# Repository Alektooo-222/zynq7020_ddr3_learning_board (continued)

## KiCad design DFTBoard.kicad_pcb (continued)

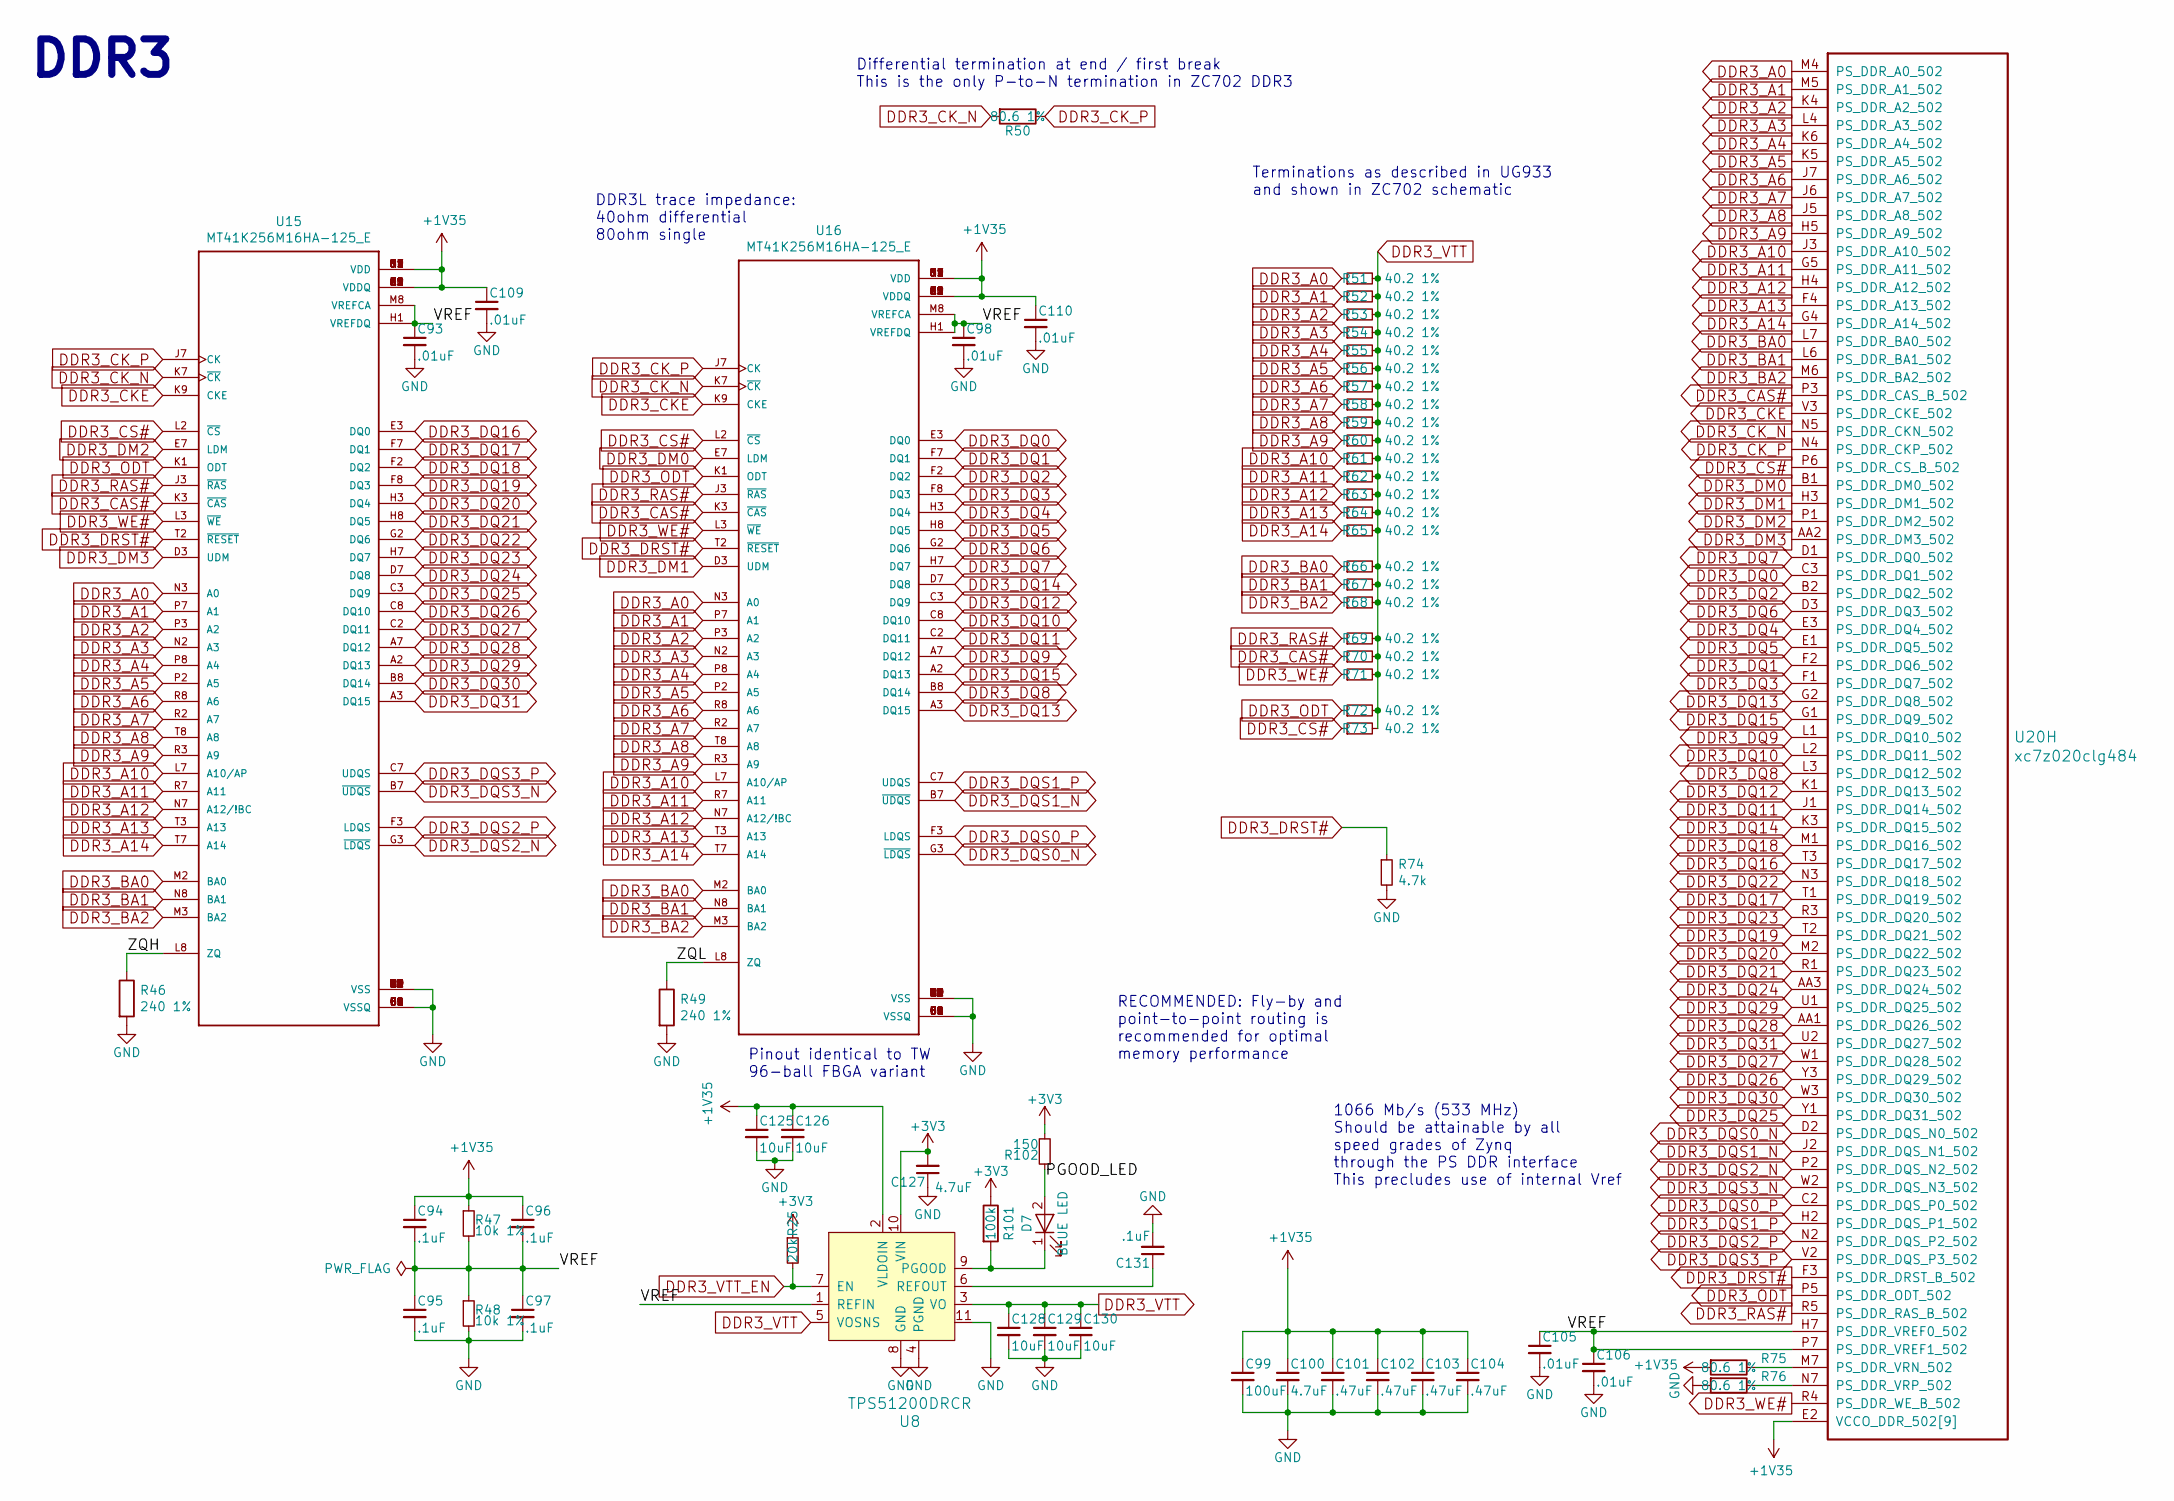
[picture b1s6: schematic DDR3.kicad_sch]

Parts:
C93, C98, C105, C106, C109, C110: .01uF; C_0402_1005Metric; MPN GRM155R71H103KA88J
C94, C95, C96, C97, C131: .1uF; C_0402_1005Metric; MPN CC0402KRX7R6BB104
C99: 100uF; C_1210_3225Metric; MPN JMK325ABJ107MM-P
C100, C127: 4.7uF; C_0402_1005Metric; MPN GRM155R60G475ME47D
C101, C102, C103, C104: .47uF; C_0402_1005Metric; MPN CC0402KRX5R5BB474
C125, C126, C128, C129, C130: 10uF; C_0603_1608Metric; MPN GRM188R61A106KE69J
D7: BLUE LED; C_0603_1608Metric; MPN VLMB1300-GS08
R25: 20k; R_0402_1005Metric; MPN RT0402BRD0720KL
R46, R49: 240 1%; R_0402_1005Metric; MPN RC0402FR-07240RL
R47, R48: 10k 1%; R_0402_1005Metric; MPN RC0402FR-0710KL
R50, R75, R76: 80.6 1%; R_0402_1005Metric; MPN RC0402FR-0780R6L
R51, R52, R53, R54, R55, R56, R57, R58, R59, R60, R61, R62, R63, R64, R65, R66, R67, R68, R69, R70, R71, R72, R73: 40.2 1%; R_0402_1005Metric; MPN RC0402FR-0740R2L
R74: 4.7k; R_0402_1005Metric; MPN RC0402JR-074K7L
R101: 100k; R_0402_1005Metric; MPN RC0402FR-07100KL
R102: 150; R_0402_1005Metric; MPN RC0402FR-07150RL
U8: TPS51200DRCR; VSON-10-1EP_3x3mm_P0.5mm_EP1.65x2.4mm_ThermalVias; MPN TPS51200DRCR; Digi-Key_PN 296-26978-1-ND
U15, U16: MT41K256M16HA-125_E; FBGA-96-DDR3-SDRAM; MPN MT41K256M16TW-107
U20: xc7z020clg484; BGA-484_19.0x19.0mm_Layout22x22_P0.80mm_dia0.40mm; MPN XC7Z020-1CLG484C

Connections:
+1V35: C94.1, C96.1, C99.1, C100.1, C101.1, C102.1, C103.1, C104.1, C109.1, C110.1, C125.1, C126.1, R47.1, R75.2, U8.2 (VLDOIN), U15.A1 (VDDQ), U15.A8 (VDDQ), U15.B2 (VDD), U15.C1 (VDDQ), U15.C9 (VDDQ), U15.D2 (VDDQ), U15.D9 (VDD), U15.E9 (VDDQ), U15.F1 (VDDQ), U15.G7 (VDD), U15.H2 (VDDQ), U15.H9 (VDDQ), U15.K2 (VDD), U15.K8 (VDD), U15.N1 (VDD), U15.N9 (VDD), U15.R1 (VDD), U15.R9 (VDD), U16.A1 (VDDQ), U16.A8 (VDDQ), U16.B2 (VDD), U16.C1 (VDDQ), U16.C9 (VDDQ), U16.D2 (VDDQ), U16.D9 (VDD), U16.E9 (VDDQ), U16.F1 (VDDQ), U16.G7 (VDD), U16.H2 (VDDQ), U16.H9 (VDDQ), U16.K2 (VDD), U16.K8 (VDD), U16.N1 (VDD), U16.N9 (VDD), U16.R1 (VDD), U16.R9 (VDD), U20.E2 (VCCO_DDR_502[9]), U20.F5 (VCCO_DDR_502[9]), U20.H1 (VCCO_DDR_502[9]), U20.J4 (VCCO_DDR_502[9]), U20.K7 (VCCO_DDR_502[9]), U20.M3 (VCCO_DDR_502[9]), U20.N6 (VCCO_DDR_502[9]), U20.R2 (VCCO_DDR_502[9]), U20.V1 (VCCO_DDR_502[9]); also elsewhere on the board
+3V3: C127.2, R25.1, R101.1, R102.2, U8.10 (VIN); also elsewhere on the board
/DDR3/PGOOD_LED: D7.2 (A), R102.1
/DDR3/VREF: C93.1, C94.2, C95.1, C96.2, C97.1, C98.1, C105.1, C106.1, R47.2, R48.1, U8.1 (REFIN), U15.H1 (VREFDQ), U15.M8 (VREFCA), U16.H1 (VREFDQ), U16.M8 (VREFCA), U20.H7 (PS_DDR_VREF0_502), U20.P7 (PS_DDR_VREF1_502)
/DDR3/ZQH: R46.1, U15.L8 (ZQ)
/DDR3/ZQL: R49.1, U16.L8 (ZQ)
DDR3_A0: R51.1, U15.N3 (A0), U16.N3 (A0), U20.M4 (PS_DDR_A0_502)
DDR3_A1: R52.1, U15.P7 (A1), U16.P7 (A1), U20.M5 (PS_DDR_A1_502)
DDR3_A2: R53.1, U15.P3 (A2), U16.P3 (A2), U20.K4 (PS_DDR_A2_502)
DDR3_A3: R54.1, U15.N2 (A3), U16.N2 (A3), U20.L4 (PS_DDR_A3_502)
DDR3_A4: R55.1, U15.P8 (A4), U16.P8 (A4), U20.K6 (PS_DDR_A4_502)
DDR3_A5: R56.1, U15.P2 (A5), U16.P2 (A5), U20.K5 (PS_DDR_A5_502)
DDR3_A6: R57.1, U15.R8 (A6), U16.R8 (A6), U20.J7 (PS_DDR_A6_502)
DDR3_A7: R58.1, U15.R2 (A7), U16.R2 (A7), U20.J6 (PS_DDR_A7_502)
DDR3_A8: R59.1, U15.T8 (A8), U16.T8 (A8), U20.J5 (PS_DDR_A8_502)
DDR3_A9: R60.1, U15.R3 (A9), U16.R3 (A9), U20.H5 (PS_DDR_A9_502)
DDR3_A10: R61.1, U15.L7 (A10/AP), U16.L7 (A10/AP), U20.J3 (PS_DDR_A10_502)
DDR3_A11: R62.1, U15.R7 (A11), U16.R7 (A11), U20.G5 (PS_DDR_A11_502)
DDR3_A12: R63.1, U15.N7 (A12/!BC), U16.N7 (A12/!BC), U20.H4 (PS_DDR_A12_502)
DDR3_A13: R64.1, U15.T3 (A13), U16.T3 (A13), U20.F4 (PS_DDR_A13_502)
DDR3_A14: R65.1, U15.T7 (A14), U16.T7 (A14), U20.G4 (PS_DDR_A14_502)
DDR3_BA0: R66.1, U15.M2 (BA0), U16.M2 (BA0), U20.L7 (PS_DDR_BA0_502)
DDR3_BA1: R67.1, U15.N8 (BA1), U16.N8 (BA1), U20.L6 (PS_DDR_BA1_502)
DDR3_BA2: R68.1, U15.M3 (BA2), U16.M3 (BA2), U20.M6 (PS_DDR_BA2_502)
DDR3_CAS#: R70.1, U15.K3 (~CAS), U16.K3 (~CAS), U20.P3 (PS_DDR_CAS_B_502)
DDR3_CKE: U15.K9 (CKE), U16.K9 (CKE), U20.V3 (PS_DDR_CKE_502)
DDR3_CK_N: R50.2, U15.K7 (~CK), U16.K7 (~CK), U20.N5 (PS_DDR_CKN_502)
DDR3_CK_P: R50.1, U15.J7 (CK), U16.J7 (CK), U20.N4 (PS_DDR_CKP_502)
DDR3_CS#: R73.1, U15.L2 (~CS), U16.L2 (~CS), U20.P6 (PS_DDR_CS_B_502)
DDR3_DM0: U16.E7 (LDM), U20.B1 (PS_DDR_DM0_502)
DDR3_DM1: U16.D3 (UDM), U20.H3 (PS_DDR_DM1_502)
DDR3_DM2: U15.E7 (LDM), U20.P1 (PS_DDR_DM2_502)
DDR3_DM3: U15.D3 (UDM), U20.AA2 (PS_DDR_DM3_502)
DDR3_DQ0: U16.E3 (DQ0), U20.C3 (PS_DDR_DQ1_502)
DDR3_DQ1: U16.F7 (DQ1), U20.F2 (PS_DDR_DQ6_502)
DDR3_DQ2: U16.F2 (DQ2), U20.B2 (PS_DDR_DQ2_502)
DDR3_DQ3: U16.F8 (DQ3), U20.F1 (PS_DDR_DQ7_502)
DDR3_DQ4: U16.H3 (DQ4), U20.E3 (PS_DDR_DQ4_502)
DDR3_DQ5: U16.H8 (DQ5), U20.E1 (PS_DDR_DQ5_502)
DDR3_DQ6: U16.G2 (DQ6), U20.D3 (PS_DDR_DQ3_502)
DDR3_DQ7: U16.H7 (DQ7), U20.D1 (PS_DDR_DQ0_502)
DDR3_DQ8: U16.B8 (DQ14), U20.L3 (PS_DDR_DQ12_502)
DDR3_DQ9: U16.A7 (DQ12), U20.L1 (PS_DDR_DQ10_502)
DDR3_DQ10: U16.C8 (DQ10), U20.L2 (PS_DDR_DQ11_502)
DDR3_DQ11: U16.C2 (DQ11), U20.J1 (PS_DDR_DQ14_502)
DDR3_DQ12: U16.C3 (DQ9), U20.K1 (PS_DDR_DQ13_502)
DDR3_DQ13: U16.A3 (DQ15), U20.G2 (PS_DDR_DQ8_502)
DDR3_DQ14: U16.D7 (DQ8), U20.K3 (PS_DDR_DQ15_502)
DDR3_DQ15: U16.A2 (DQ13), U20.G1 (PS_DDR_DQ9_502)
DDR3_DQ16: U15.E3 (DQ0), U20.T3 (PS_DDR_DQ17_502)
DDR3_DQ17: U15.F7 (DQ1), U20.T1 (PS_DDR_DQ19_502)
DDR3_DQ18: U15.F2 (DQ2), U20.M1 (PS_DDR_DQ16_502)
DDR3_DQ19: U15.F8 (DQ3), U20.T2 (PS_DDR_DQ21_502)
DDR3_DQ20: U15.H3 (DQ4), U20.M2 (PS_DDR_DQ22_502)
DDR3_DQ21: U15.H8 (DQ5), U20.R1 (PS_DDR_DQ23_502)
DDR3_DQ22: U15.G2 (DQ6), U20.N3 (PS_DDR_DQ18_502)
DDR3_DQ23: U15.H7 (DQ7), U20.R3 (PS_DDR_DQ20_502)
DDR3_DQ24: U15.D7 (DQ8), U20.AA3 (PS_DDR_DQ24_502)
DDR3_DQ25: U15.C3 (DQ9), U20.Y1 (PS_DDR_DQ31_502)
DDR3_DQ26: U15.C8 (DQ10), U20.Y3 (PS_DDR_DQ29_502)
DDR3_DQ27: U15.C2 (DQ11), U20.W1 (PS_DDR_DQ28_502)
DDR3_DQ28: U15.A7 (DQ12), U20.AA1 (PS_DDR_DQ26_502)
DDR3_DQ29: U15.A2 (DQ13), U20.U1 (PS_DDR_DQ25_502)
DDR3_DQ30: U15.B8 (DQ14), U20.W3 (PS_DDR_DQ30_502)
DDR3_DQ31: U15.A3 (DQ15), U20.U2 (PS_DDR_DQ27_502)
DDR3_DQS0_N: U16.G3 (~LDQS), U20.D2 (PS_DDR_DQS_N0_502)
DDR3_DQS0_P: U16.F3 (LDQS), U20.C2 (PS_DDR_DQS_P0_502)
DDR3_DQS1_N: U16.B7 (~UDQS), U20.J2 (PS_DDR_DQS_N1_502)
DDR3_DQS1_P: U16.C7 (UDQS), U20.H2 (PS_DDR_DQS_P1_502)
DDR3_DQS2_N: U15.G3 (~LDQS), U20.P2 (PS_DDR_DQS_N2_502)
DDR3_DQS2_P: U15.F3 (LDQS), U20.N2 (PS_DDR_DQS_P2_502)
DDR3_DQS3_N: U15.B7 (~UDQS), U20.W2 (PS_DDR_DQS_N3_502)
DDR3_DQS3_P: U15.C7 (UDQS), U20.V2 (PS_DDR_DQS_P3_502)
DDR3_DRST#: R74.1, U15.T2 (~RESET), U16.T2 (~RESET), U20.F3 (PS_DDR_DRST_B_502)
DDR3_ODT: R72.1, U15.K1 (ODT), U16.K1 (ODT), U20.P5 (PS_DDR_ODT_502)
DDR3_RAS#: R69.1, U15.J3 (~RAS), U16.J3 (~RAS), U20.R5 (PS_DDR_RAS_B_502)
DDR3_VTT: C128.1, C129.1, C130.1, R51.2, R52.2, R53.2, R54.2, R55.2, R56.2, R57.2, R58.2, R59.2, R60.2, R61.2, R62.2, R63.2, R64.2, R65.2, R66.2, R67.2, R68.2, R69.2, R70.2, R71.2, R72.2, R73.2, U8.3 (VO), U8.5 (VOSNS)
DDR3_VTT_EN: R25.2, U8.7 (EN); also elsewhere on the board
DDR3_WE#: R71.1, U15.L3 (~WE), U16.L3 (~WE), U20.R4 (PS_DDR_WE_B_502)
GND: C93.2, C95.2, C97.2, C98.2, C99.2, C100.2, C101.2, C102.2, C103.2, C104.2, C105.2, C106.2, C109.2, C110.2, C125.2, C126.2, C127.1, C128.2, C129.2, C130.2, C131.2, R46.2, R48.2, R49.2, R74.2, R76.2, U8.4 (PGND), U8.8 (GND), U8.11, U15.A9 (VSS), U15.B1 (VSSQ), U15.B3 (VSS), U15.B9 (VSSQ), U15.D1 (VSSQ), U15.D8 (VSSQ), U15.E1 (VSS), U15.E2 (VSSQ), U15.E8 (VSSQ), U15.F9 (VSSQ), U15.G1 (VSSQ), U15.G8 (VSS), U15.G9 (VSSQ), U15.J2 (VSS), U15.J8 (VSS), U15.M1 (VSS), U15.M9 (VSS), U15.P1 (VSS), U15.P9 (VSS), U15.T1 (VSS), U15.T9 (VSS), U16.A9 (VSS), U16.B1 (VSSQ), U16.B3 (VSS), U16.B9 (VSSQ), U16.D1 (VSSQ), U16.D8 (VSSQ), U16.E1 (VSS), U16.E2 (VSSQ), U16.E8 (VSSQ), U16.F9 (VSSQ), U16.G1 (VSSQ), U16.G8 (VSS), U16.G9 (VSSQ), U16.J2 (VSS), U16.J8 (VSS), U16.M1 (VSS), U16.M9 (VSS), U16.P1 (VSS), U16.P9 (VSS), U16.T1 (VSS), U16.T9 (VSS); also elsewhere on the board
unnamed: D7.1 (K), R101.2, U8.9 (PGOOD)
unnamed: C131.1, U8.6 (REFOUT)
unnamed: R75.1, U20.M7 (PS_DDR_VRN_502)
unnamed: R76.1, U20.N7 (PS_DDR_VRP_502)

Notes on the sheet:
1066 Mb/s (533 MHz) Should be attainable by all speed grades of Zynq through the PS DDR interface This precludes use of internal Vref
DDR3L trace impedance: 40ohm differential 80ohm single
Terminations as described in UG933 and shown in ZC702 schematic
Pinout identical to TW 96-ball FBGA variant
RECOMMENDED: Fly-by and point-to-point routing is recommended for optimal memory performance
DDR3
Differential termination at end / first break This is the only P-to-N termination in ZC702 DDR3

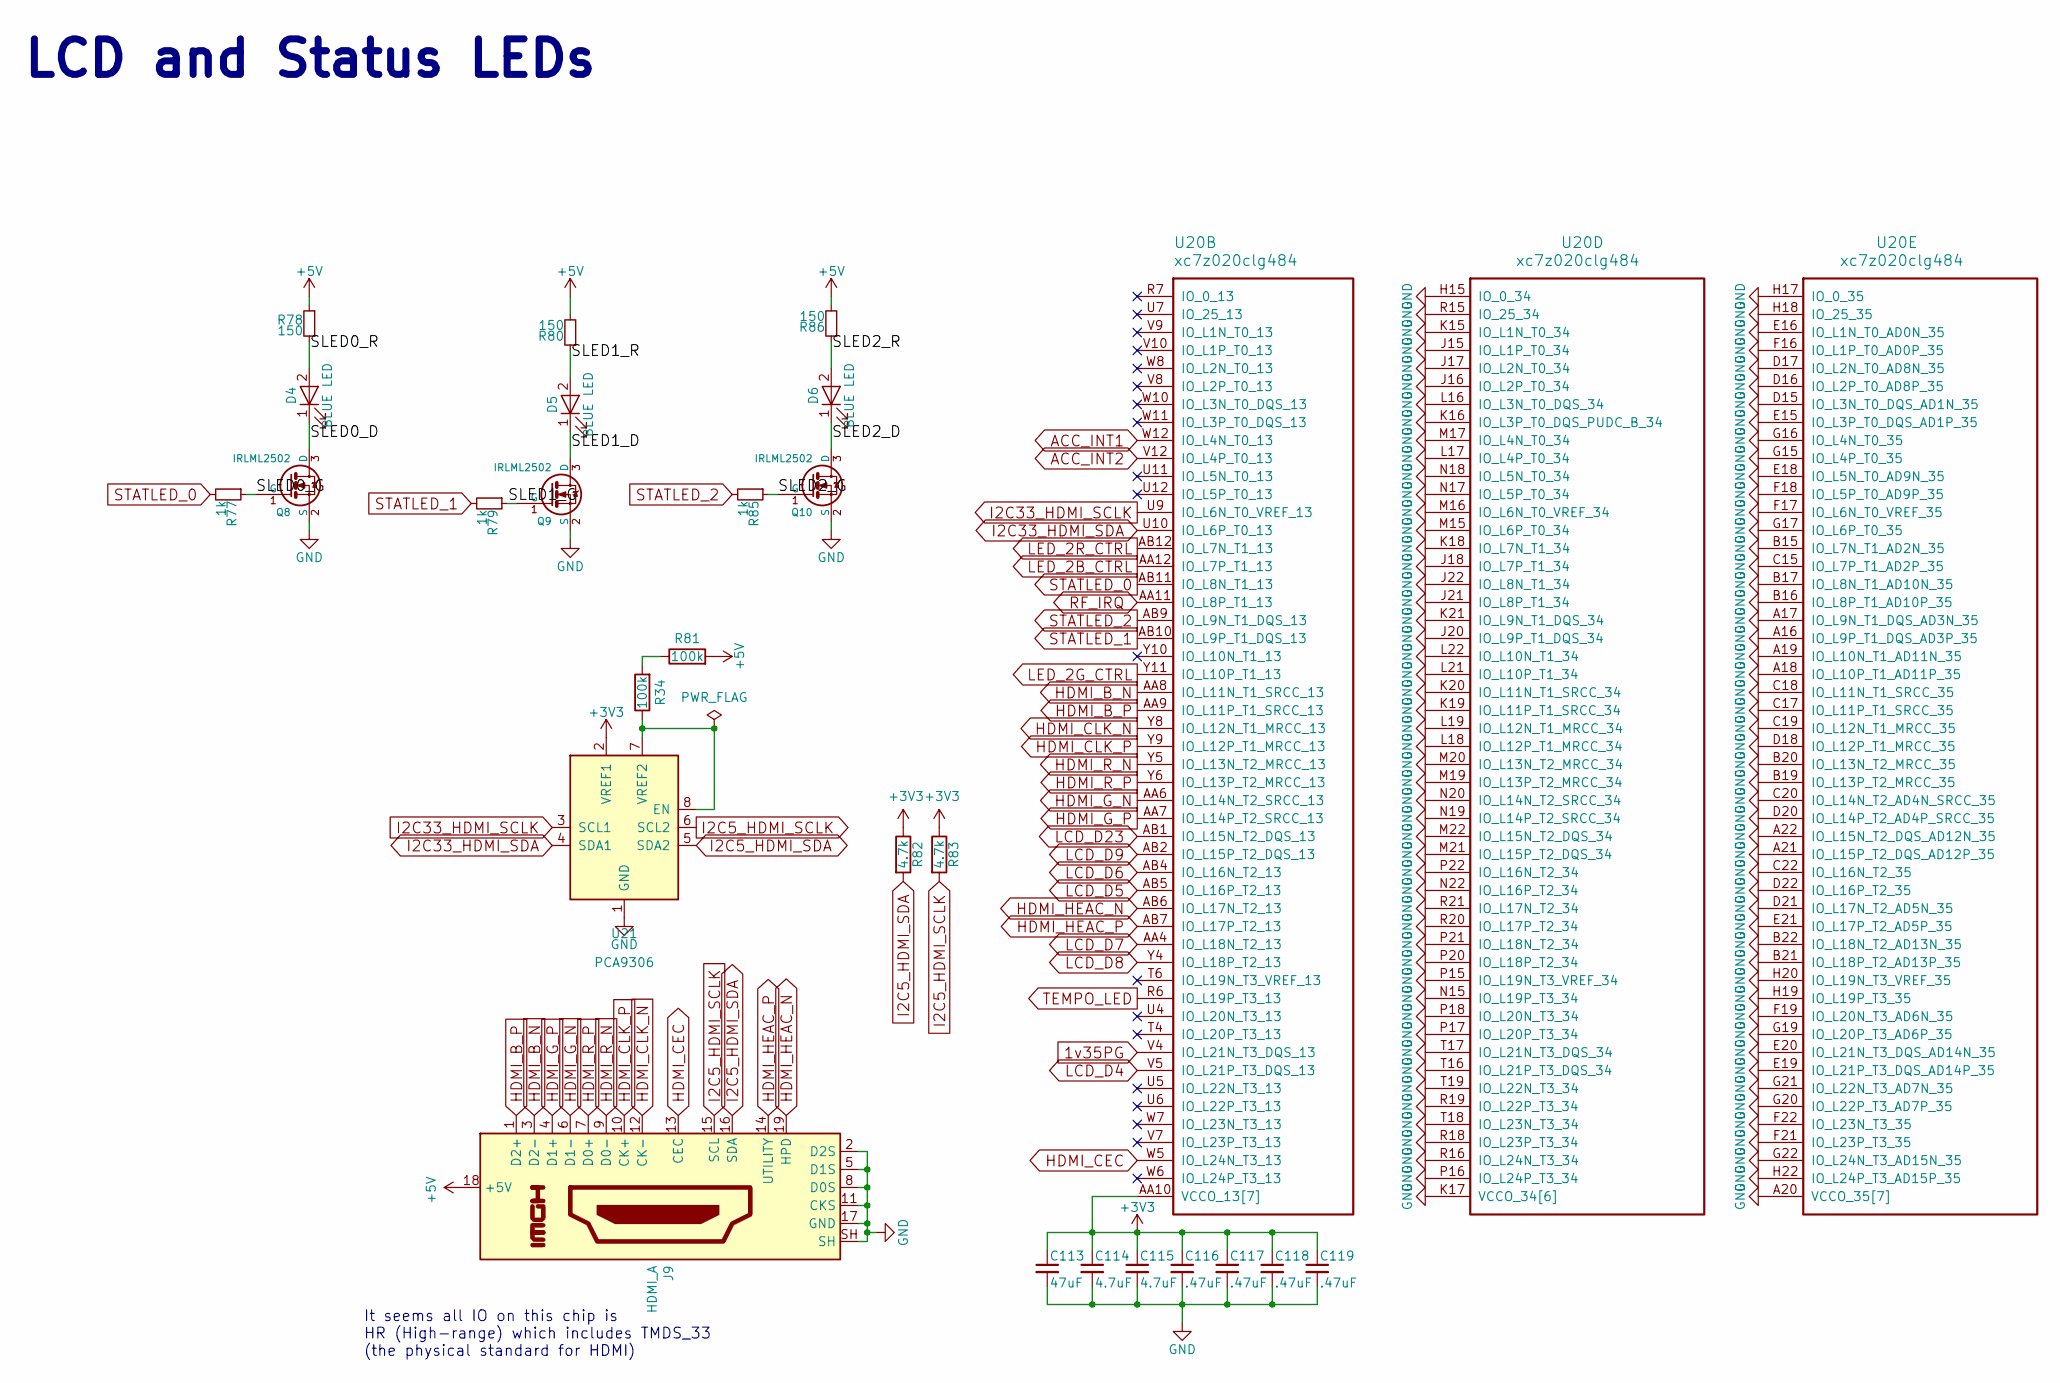
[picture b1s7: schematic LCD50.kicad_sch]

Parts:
C113: 47uF; C_1210_3225Metric; MPN GRM32ER70J476ME20L
C114, C115: 4.7uF; C_0402_1005Metric; MPN GRM155R60G475ME47D
C116, C117, C118, C119: .47uF; C_0402_1005Metric; MPN CC0402KRX5R5BB474
D4, D5, D6: BLUE LED; C_0603_1608Metric; MPN VLMB1300-GS08
J9: HDMI_A; 10029449-111RLF; MPN 10029449-111RLF
Q8, Q9, Q10: IRLML2502; SOT-23; MPN IRLML2502TRPBF
R34, R81: 100k; R_0402_1005Metric; MPN RC0402FR-07100KL
R77, R79, R85: 1k; R_0402_1005Metric; MPN RC0402FR-071KL
R78, R80, R86: 150; R_0402_1005Metric; MPN RC0402FR-07150RL
R82, R83: 4.7k; R_0402_1005Metric; MPN RC0402JR-074K7L
U20: xc7z020clg484; BGA-484_19.0x19.0mm_Layout22x22_P0.80mm_dia0.40mm; MPN XC7Z020-1CLG484C
U21: PCA9306; SSOP-8_2.95x2.8mm_P0.65mm; MPN PCA9306DCTR

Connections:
1v35PG: U20.V4 (IO_L21N_T3_DQS_13); also elsewhere on the board
+3V3: C113.1, C114.1, C115.1, C116.1, C117.1, C118.1, C119.1, R82.1, R83.1, U20.AA10 (VCCO_13[7]), U20.AB3 (VCCO_13[7]), U20.T5 (VCCO_13[7]), U20.U8 (VCCO_13[7]), U20.V11 (VCCO_13[7]), U20.W4 (VCCO_13[7]), U20.Y7 (VCCO_13[7]), U21.2 (VREF1); also elsewhere on the board
+5V: J9.18 (+5V), R78.1, R80.2, R81.2, R86.2; also elsewhere on the board
/LCD50/SLED0_D: D4.1 (K), Q8.3 (D)
/LCD50/SLED0_G: Q8.1 (G), R77.1
/LCD50/SLED0_R: D4.2 (A), R78.2
/LCD50/SLED1_D: D5.1 (K), Q9.3 (D)
/LCD50/SLED1_G: Q9.1 (G), R79.1
/LCD50/SLED1_R: D5.2 (A), R80.1
/LCD50/SLED2_D: D6.1 (K), Q10.3 (D)
/LCD50/SLED2_G: Q10.1 (G), R85.1
/LCD50/SLED2_R: D6.2 (A), R86.1
ACC_INT1: U20.W12 (IO_L4N_T0_13); also elsewhere on the board
ACC_INT2: U20.V12 (IO_L4P_T0_13); also elsewhere on the board
GND: C113.2, C114.2, C115.2, C116.2, C117.2, C118.2, C119.2, J9.2 (D2S), J9.5 (D1S), J9.8 (D0S), J9.11 (CKS), J9.17 (GND), J9.SH, Q8.2 (S), Q9.2 (S), Q10.2 (S), U20.A16 (IO_L9P_T1_DQS_AD3P_35), U20.A17 (IO_L9N_T1_DQS_AD3N_35), U20.A18 (IO_L10P_T1_AD11P_35), U20.A19 (IO_L10N_T1_AD11N_35), U20.A20 (VCCO_35[7]), U20.A21 (IO_L15P_T2_DQS_AD12P_35), U20.A22 (IO_L15N_T2_DQS_AD12N_35), U20.B15 (IO_L7N_T1_AD2N_35), U20.B16 (IO_L8P_T1_AD10P_35), U20.B17 (IO_L8N_T1_AD10N_35), U20.B19 (IO_L13P_T2_MRCC_35), U20.B20 (IO_L13N_T2_MRCC_35), U20.B21 (IO_L18P_T2_AD13P_35), U20.B22 (IO_L18N_T2_AD13N_35), U20.C15 (IO_L7P_T1_AD2P_35), U20.C16 (VCCO_35[7]), U20.C17 (IO_L11P_T1_SRCC_35), U20.C18 (IO_L11N_T1_SRCC_35), U20.C19 (IO_L12N_T1_MRCC_35), U20.C20 (IO_L14N_T2_AD4N_SRCC_35), U20.C22 (IO_L16N_T2_35), U20.D15 (IO_L3N_T0_DQS_AD1N_35), U20.D16 (IO_L2P_T0_AD8P_35), U20.D17 (IO_L2N_T0_AD8N_35), U20.D18 (IO_L12P_T1_MRCC_35), U20.D19 (VCCO_35[7]), U20.D20 (IO_L14P_T2_AD4P_SRCC_35), U20.D21 (IO_L17N_T2_AD5N_35), U20.D22 (IO_L16P_T2_35), U20.E15 (IO_L3P_T0_DQS_AD1P_35), U20.E16 (IO_L1N_T0_AD0N_35), U20.E18 (IO_L5N_T0_AD9N_35), U20.E19 (IO_L21P_T3_DQS_AD14P_35), U20.E20 (IO_L21N_T3_DQS_AD14N_35), U20.E21 (IO_L17P_T2_AD5P_35), U20.E22 (VCCO_35[7]), U20.F15 (VCCO_35[7]), U20.F16 (IO_L1P_T0_AD0P_35), U20.F17 (IO_L6N_T0_VREF_35), U20.F18 (IO_L5P_T0_AD9P_35), U20.F19 (IO_L20N_T3_AD6N_35), U20.F21 (IO_L23P_T3_35), U20.F22 (IO_L23N_T3_35), U20.G15 (IO_L4P_T0_35), U20.G16 (IO_L4N_T0_35), U20.G17 (IO_L6P_T0_35), U20.G18 (VCCO_35[7]), U20.G19 (IO_L20P_T3_AD6P_35), U20.G20 (IO_L22P_T3_AD7P_35), U20.G21 (IO_L22N_T3_AD7N_35), U20.G22 (IO_L24N_T3_AD15N_35), U20.H15 (IO_0_34), U20.H17 (IO_0_35), U20.H18 (IO_25_35), U20.H19 (IO_L19P_T3_35), U20.H20 (IO_L19N_T3_VREF_35), U20.H21 (VCCO_35[7]), U20.H22 (IO_L24P_T3_AD15P_35), U20.J15 (IO_L1P_T0_34), U20.J16 (IO_L2P_T0_34), U20.J17 (IO_L2N_T0_34), U20.J18 (IO_L7P_T1_34), U20.J20 (IO_L9P_T1_DQS_34), U20.J21 (IO_L8P_T1_34), U20.J22 (IO_L8N_T1_34), U20.K15 (IO_L1N_T0_34), U20.K16 (IO_L3P_T0_DQS_PUDC_B_34), U20.K17 (VCCO_34[6]), U20.K18 (IO_L7N_T1_34), U20.K19 (IO_L11P_T1_SRCC_34), U20.K20 (IO_L11N_T1_SRCC_34), U20.K21 (IO_L9N_T1_DQS_34), U20.L16 (IO_L3N_T0_DQS_34), U20.L17 (IO_L4P_T0_34), U20.L18 (IO_L12P_T1_MRCC_34), U20.L19 (IO_L12N_T1_MRCC_34), U20.L20 (VCCO_34[6]), U20.L21 (IO_L10P_T1_34), U20.L22 (IO_L10N_T1_34), U20.M15 (IO_L6P_T0_34), U20.M16 (IO_L6N_T0_VREF_34), U20.M17 (IO_L4N_T0_34), U20.M19 (IO_L13P_T2_MRCC_34), U20.M20 (IO_L13N_T2_MRCC_34), U20.M21 (IO_L15P_T2_DQS_34), U20.M22 (IO_L15N_T2_DQS_34), U20.N15 (IO_L19P_T3_34), U20.N16 (VCCO_34[6]), U20.N17 (IO_L5P_T0_34), U20.N18 (IO_L5N_T0_34), U20.N19 (IO_L14P_T2_SRCC_34), U20.N20 (IO_L14N_T2_SRCC_34), U20.N22 (IO_L16P_T2_34), U20.P15 (IO_L19N_T3_VREF_34), U20.P16 (IO_L24P_T3_34), U20.P17 (IO_L20P_T3_34), U20.P18 (IO_L20N_T3_34), U20.P19 (VCCO_34[6]), U20.P20 (IO_L18P_T2_34), U20.P21 (IO_L18N_T2_34), U20.P22 (IO_L16N_T2_34), U20.R15 (IO_25_34), U20.R16 (IO_L24N_T3_34), U20.R18 (IO_L23P_T3_34), U20.R19 (IO_L22P_T3_34), U20.R20 (IO_L17P_T2_34), U20.R21 (IO_L17N_T2_34), U20.R22 (VCCO_34[6]), U20.T15 (VCCO_34[6]), U20.T16 (IO_L21P_T3_DQS_34), U20.T17 (IO_L21N_T3_DQS_34), U20.T18 (IO_L23N_T3_34), U20.T19 (IO_L22N_T3_34), U21.1 (GND); also elsewhere on the board
HDMI_B_N: J9.3 (D2-), U20.AA8 (IO_L11N_T1_SRCC_13)
HDMI_B_P: J9.1 (D2+), U20.AA9 (IO_L11P_T1_SRCC_13)
HDMI_CEC: J9.13 (CEC), U20.W5 (IO_L24N_T3_13)
HDMI_CLK_N: J9.12 (CK-), U20.Y8 (IO_L12N_T1_MRCC_13)
HDMI_CLK_P: J9.10 (CK+), U20.Y9 (IO_L12P_T1_MRCC_13)
HDMI_G_N: J9.6 (D1-), U20.AA6 (IO_L14N_T2_SRCC_13)
HDMI_G_P: J9.4 (D1+), U20.AA7 (IO_L14P_T2_SRCC_13)
HDMI_HEAC_N: J9.19 (HPD), U20.AB6 (IO_L17N_T2_13)
HDMI_HEAC_P: J9.14 (UTILITY), U20.AB7 (IO_L17P_T2_13)
HDMI_R_N: J9.9 (D0-), U20.Y5 (IO_L13N_T2_MRCC_13)
HDMI_R_P: J9.7 (D0+), U20.Y6 (IO_L13P_T2_MRCC_13)
I2C5_HDMI_SCLK: J9.15 (SCL), R83.2, U21.6 (SCL2)
I2C5_HDMI_SDA: J9.16 (SDA), R82.2, U21.5 (SDA2)
I2C33_HDMI_SCLK: U20.U9 (IO_L6N_T0_VREF_13), U21.3 (SCL1)
I2C33_HDMI_SDA: U20.U10 (IO_L6P_T0_13), U21.4 (SDA1)
LCD_D4: U20.V5 (IO_L21P_T3_DQS_13)
LCD_D5: U20.AB5 (IO_L16P_T2_13)
LCD_D6: U20.AB4 (IO_L16N_T2_13)
LCD_D7: U20.AA4 (IO_L18N_T2_13)
LCD_D8: U20.Y4 (IO_L18P_T2_13)
LCD_D9: U20.AB2 (IO_L15P_T2_DQS_13)
LCD_D23: U20.AB1 (IO_L15N_T2_DQS_13)
LED_2B_CTRL: U20.AA12 (IO_L7P_T1_13)
LED_2G_CTRL: U20.Y11 (IO_L10P_T1_13)
LED_2R_CTRL: U20.AB12 (IO_L7N_T1_13)
unnamed: R34.2, R81.1
unnamed: R34.1, U21.7 (VREF2), U21.8 (EN)
RF_IRQ: U20.AA11 (IO_L8P_T1_13); also elsewhere on the board
STATLED_0: R77.2, U20.AB11 (IO_L8N_T1_13)
STATLED_1: R79.2, U20.AB10 (IO_L9P_T1_DQS_13)
STATLED_2: R85.2, U20.AB9 (IO_L9N_T1_DQS_13)
TEMPO_LED: U20.R6 (IO_L19P_T3_13); also elsewhere on the board

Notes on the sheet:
It seems all IO on this chip is HR (High-range) which includes TMDS_33 (the physical standard for HDMI)
LCD and Status LEDs

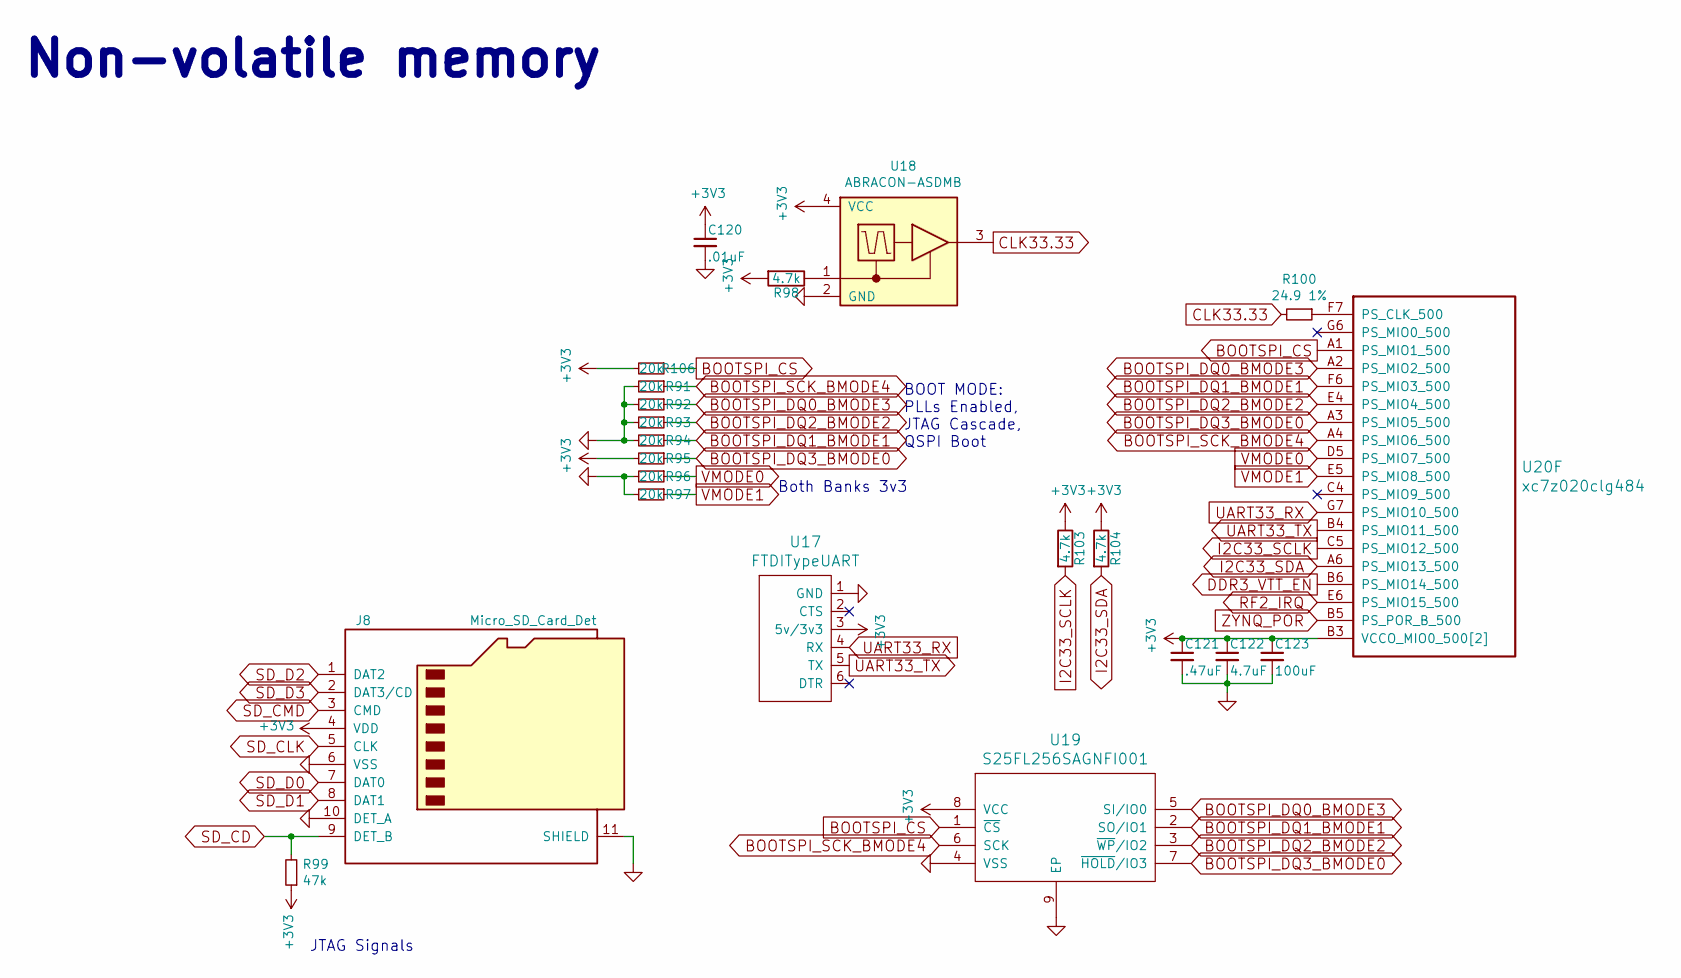
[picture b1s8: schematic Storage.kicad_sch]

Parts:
C120: .01uF; C_0402_1005Metric; MPN GRM155R71H103KA88J
C121: .47uF; C_0402_1005Metric; MPN CC0402KRX5R5BB474
C122: 4.7uF; C_0402_1005Metric; MPN GRM155R60G475ME47D
C123: 100uF; C_1210_3225Metric; MPN JMK325ABJ107MM-P
J8: Micro_SD_Card_Det; AMPHENOL-114-00841-68; MPN 114-00841-68
R91, R92, R93, R94, R95, R96, R97, R106: 20k; R_0402_1005Metric; MPN RT0402BRD0720KL
R98, R103, R104: 4.7k; R_0402_1005Metric; MPN RC0402JR-074K7L
R99: 47k; R_0402_1005Metric; MPN RC0402FR-0747KL
R100: 24.9 1%; R_0402_1005Metric; MPN RC0402FR-0724K9L
U17: FTDITypeUART; FTDI_CONN
U18: ABRACON-ASDMB; XTAL_ASDMB-24.000MHZ-LC-T; MPN ASDMB-24.000MHZ-LC-T
U19: S25FL256SAGNFI001; DFN-8-1EP_2x2mm_P0.5mm_EP0.7x1.3mm; MPN S25FL256SAGNFI001
U20: xc7z020clg484; BGA-484_19.0x19.0mm_Layout22x22_P0.80mm_dia0.40mm; MPN XC7Z020-1CLG484C

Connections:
+3V3: C120.1, C121.1, C122.1, C123.1, J8.4 (VDD), R95.2, R98.2, R99.1, R103.1, R104.1, R106.2, U17.3 (5v/3v3), U18.4 (VCC), U19.8 (VCC), U20.B3 (VCCO_MIO0_500[2]), U20.C6 (VCCO_MIO0_500[2]); also elsewhere on the board
BOOTSPI_CS: R106.1, U19.1 (~CS), U20.A1 (PS_MIO1_500)
BOOTSPI_DQ0_BMODE3: R92.1, U19.5 (SI/IO0), U20.A2 (PS_MIO2_500)
BOOTSPI_DQ1_BMODE1: R94.1, U19.2 (SO/IO1), U20.F6 (PS_MIO3_500)
BOOTSPI_DQ2_BMODE2: R93.1, U19.3 (~WP/IO2), U20.E4 (PS_MIO4_500)
BOOTSPI_DQ3_BMODE0: R95.1, U19.7 (~HOLD/IO3), U20.A3 (PS_MIO5_500)
BOOTSPI_SCK_BMODE4: R91.1, U19.6 (SCK), U20.A4 (PS_MIO6_500)
CLK33.33: R100.2, U18.3 (OUT)
DDR3_VTT_EN: U20.B6 (PS_MIO14_500); also elsewhere on the board
GND: C120.2, C121.2, C122.2, C123.2, J8.6 (VSS), J8.10 (DET_A), J8.11 (SHIELD), R91.2, R92.2, R93.2, R94.2, R96.2, R97.2, U17.1 (GND), U18.2 (GND), U19.4 (VSS), U19.9 (EP); also elsewhere on the board
I2C33_SCLK: R103.2, U20.C5 (PS_MIO12_500); also elsewhere on the board
I2C33_SDA: R104.2, U20.A6 (PS_MIO13_500); also elsewhere on the board
unnamed: R98.1, U18.1 (OE)
unnamed: R100.1, U20.F7 (PS_CLK_500)
RF2_IRQ: U20.E6 (PS_MIO15_500); also elsewhere on the board
SD_CD: J8.9 (DET_B), R99.2; also elsewhere on the board
SD_CLK: J8.5 (CLK); also elsewhere on the board
SD_CMD: J8.3 (CMD); also elsewhere on the board
SD_D0: J8.7 (DAT0); also elsewhere on the board
SD_D1: J8.8 (DAT1); also elsewhere on the board
SD_D2: J8.1 (DAT2); also elsewhere on the board
SD_D3: J8.2 (DAT3/CD); also elsewhere on the board
UART33_RX: U17.4 (RX), U20.G7 (PS_MIO10_500)
UART33_TX: U17.5 (TX), U20.B4 (PS_MIO11_500)
VMODE0: R96.1, U20.D5 (PS_MIO7_500)
VMODE1: R97.1, U20.E5 (PS_MIO8_500)
ZYNQ_POR: U20.B5 (PS_POR_B_500); also elsewhere on the board

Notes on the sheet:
BOOT MODE: PLLs Enabled, JTAG Cascade, QSPI Boot
Both Banks 3v3
JTAG Signals
Non-volatile memory

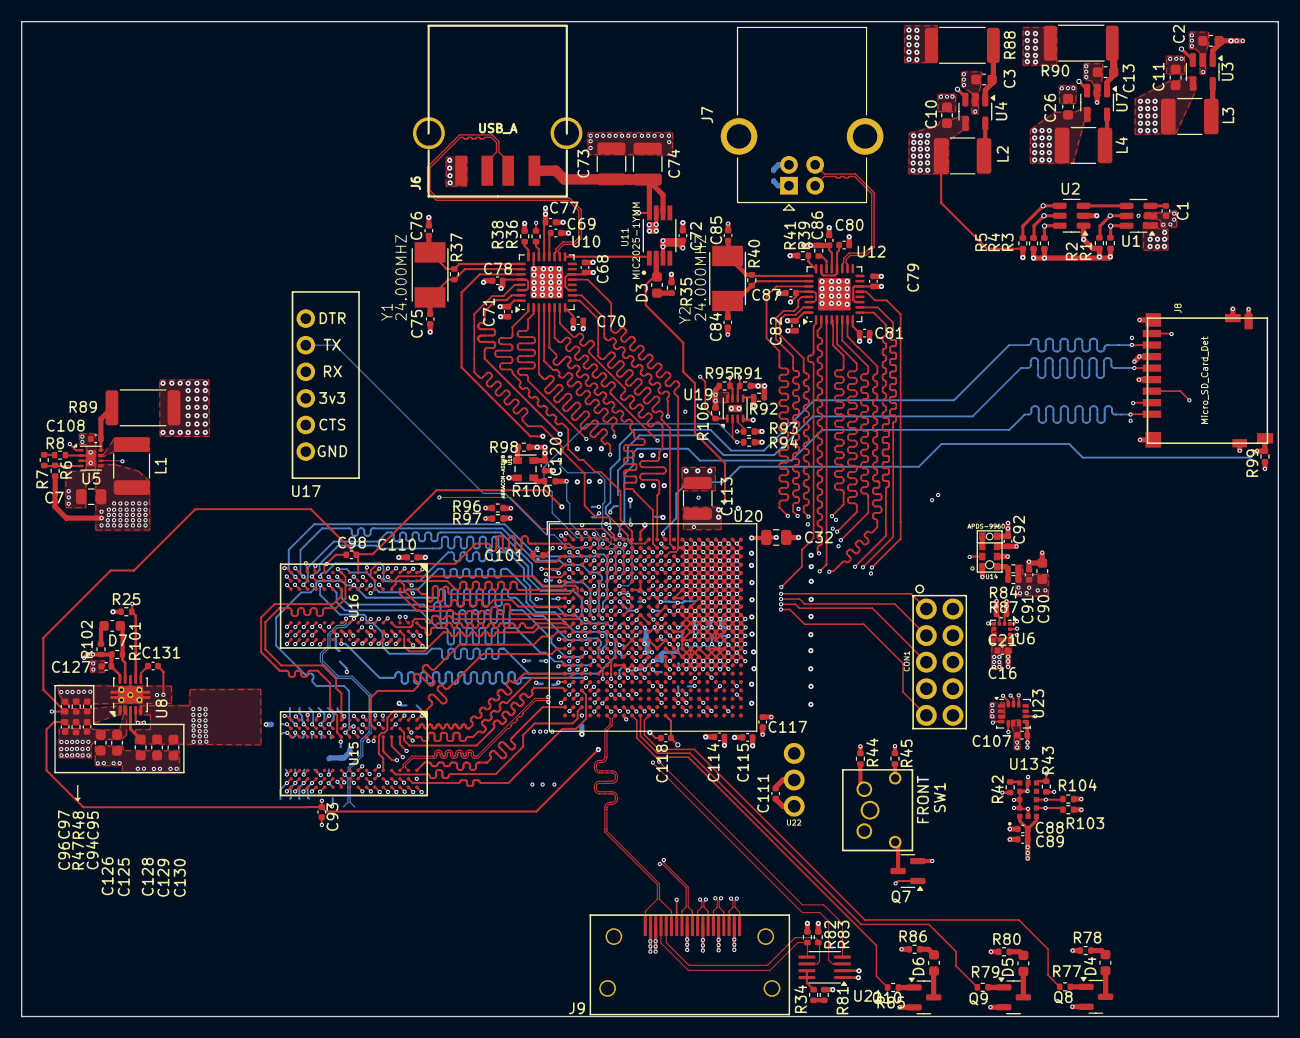
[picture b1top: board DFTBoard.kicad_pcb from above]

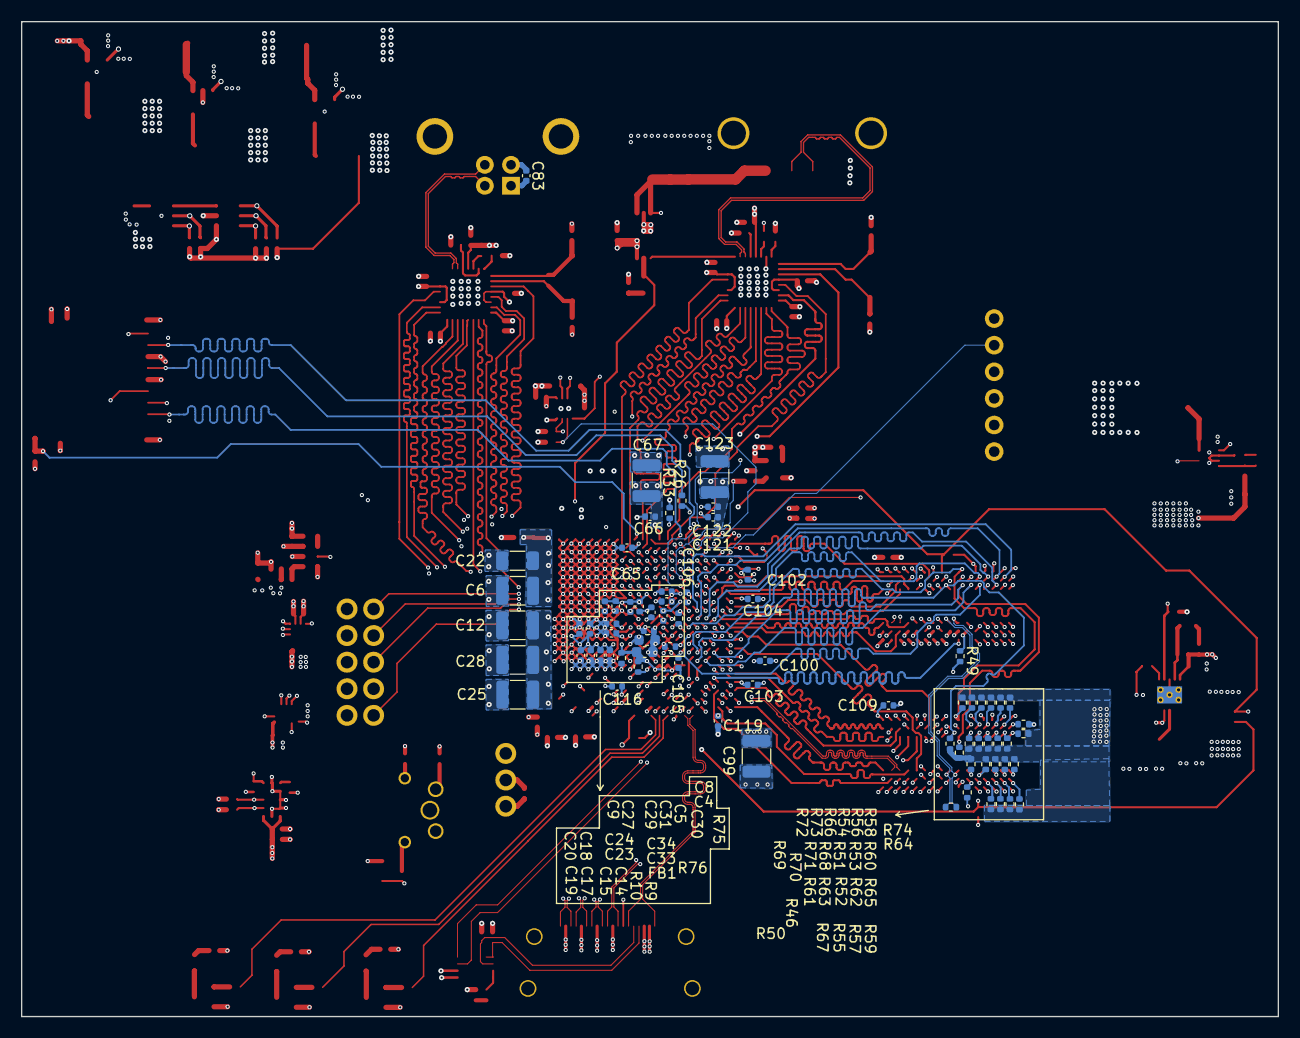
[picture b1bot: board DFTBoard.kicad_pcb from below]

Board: 8 copper layers, 120.0 x 95.0 mm, 228 parts (74 on the bottom side), 222 nets.
